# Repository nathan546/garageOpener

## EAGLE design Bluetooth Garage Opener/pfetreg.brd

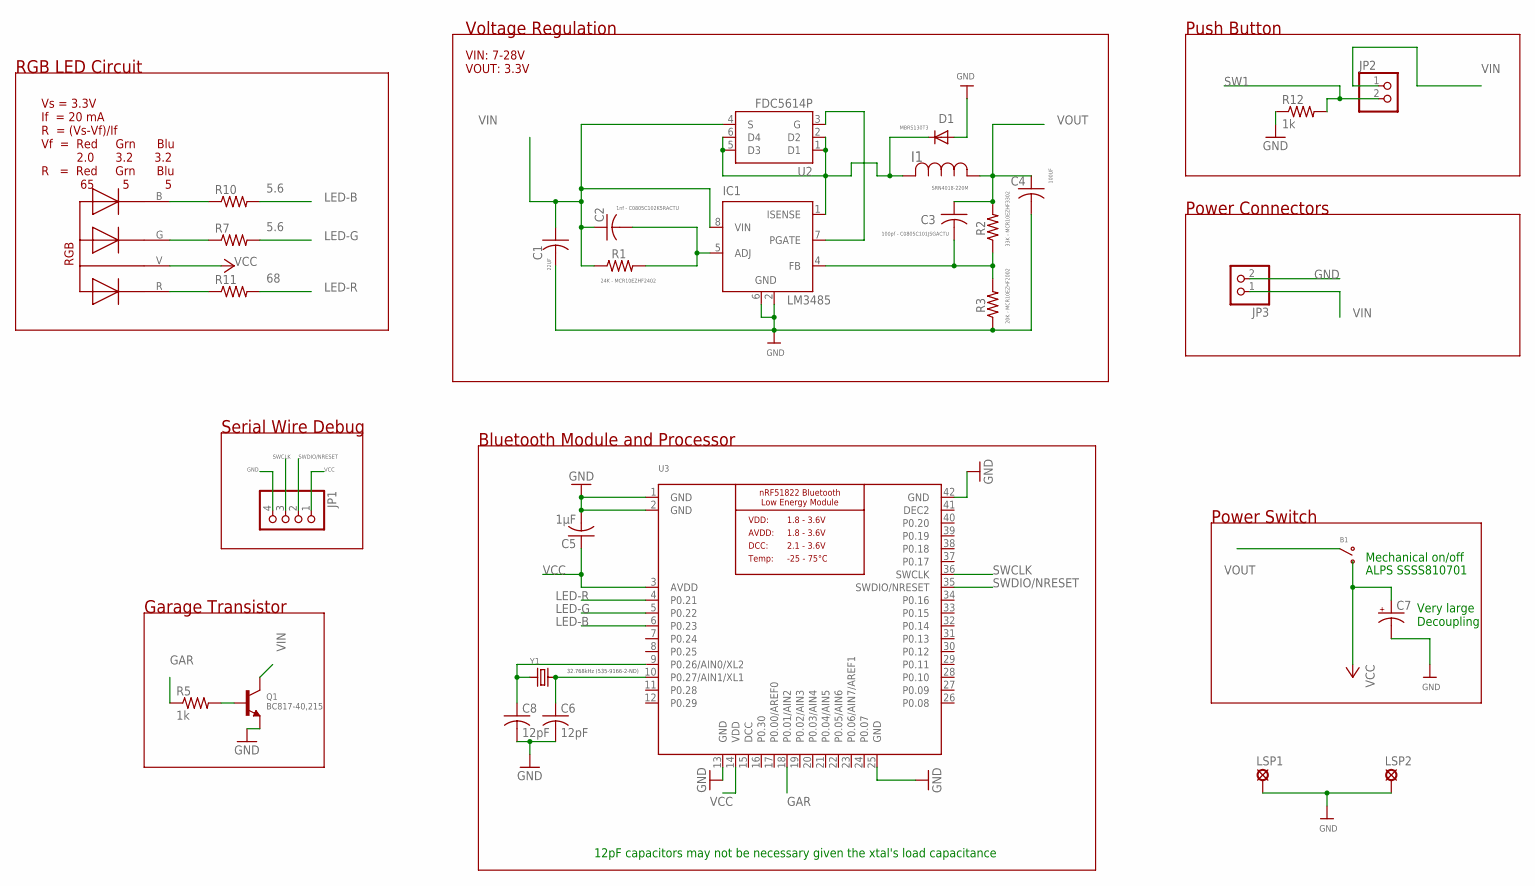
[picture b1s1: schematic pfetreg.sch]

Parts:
B1: SSSS810701
C1: 22UF; CAPCP7343X430N
C2: 1nf - C0805C102K5RACTU; C0805K
C3: 100pf - C0805C101J5GACTU; C0805K
C4: 100UF; CAPCP7343X430N
C5: 1µF; C0805K
C6, C8: 12pF; C0805
C7: CPOL-USE5-10.5; E5-10,5
D1: MBRS130T3; DO214AA
I1: SRN4018-220M
IC1: LM3485; MSOP08
JP1: PINHD-1X4; 1X04
JP2, JP3: PINHD-1X2; 1X02
LSP1, LSP2: LSP11
Q1: BC817-40,215; SOT23-R
R1: 24K - MCR10EZHF2402; R0805W
R2: 33K - MCR10EZHF3302; R0805W
R3: 20K - MCR10EZHF2002; R0805W
R5, R12: 1k; R0805
R7, R10: 5.6; R0805
R11: 68; R0805
RGB: 5MMRGBLED; LED5MMRGB
U2: FDC5614PSOT-23; SOT23-6
U3: NRF51822_MODULE_MDBT40; BLE_MODULE_RAYTAC_MDBT40
Y1: CRYSTAL8X3.8SMT; CRYSTAL_8X3.8

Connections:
DCC: U3.15 (DCC)
DEC2: U3.41 (DEC2)
GAR: R5.1, U3.18 (P0.01/AIN2)
GND: C1.2 (I2), C4.2 (I2), C5.2, C6.2, C7.-, C8.2, D1.A, IC1.2 (GND), IC1.6 (GND), JP1.4, JP3.2, LSP1.MP, LSP2.MP, Q1.2 (E), R3.1, R12.1, U3.1 (GND), U3.2 (GND), U3.13 (GND), U3.25 (GND), U3.42 (GND)
LED-B: R10.2, U3.6 (P0.23)
LED-G: R7.2, U3.5 (P0.22)
LED-R: R11.2, U3.4 (P0.21)
unnamed: D1.C, I1.1 (I1), IC1.1 (ISENSE), U2.1 (D1), U2.2 (D2), U2.5 (D3), U2.6 (D4)
unnamed: C3.2, IC1.4 (FB), R2.1, R3.2
unnamed: IC1.7 (PGATE), U2.3 (G)
unnamed: C2.2, IC1.5 (ADJ), R1.2
unnamed: Q1.1 (B), R5.2
unnamed: R7.1, RGB.G
unnamed: R10.1, RGB.B
unnamed: R11.1, RGB.R
unnamed: C8.1, U3.9 (P0.26/AIN0/XL2), Y1.P$1 (1)
unnamed: C6.1, U3.10 (P0.27/AIN1/XL1), Y1.P$4 (2)
SW1: JP2.2, R12.2
SWCLK: JP1.3, U3.36 (SWCLK)
SWDIO/NRESET: JP1.2, U3.35 (SWDIO/NRESET)
VCC: B1.1 (B), C5.1, C7.+, JP1.1, RGB.V, U3.3 (AVDD), U3.14 (VDD)
VIN: C1.1 (I1), C2.1, IC1.8 (VIN), JP2.1, JP3.1, Q1.3 (C), R1.1, U2.4 (S)
VOUT: B1.2 (COM), C3.1, C4.1 (I1), I1.2 (I2), R2.2

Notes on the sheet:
VIN: 7-28V VOUT: 3.3V
32.768kHz (535-9166-2-ND)
Bluetooth Module and Processor
12pF capacitors may not be necessary given the xtal's load capacitance
Vs = 3.3V If = 20 mA R = (Vs-Vf)/If Vf = Red Grn Blu 2.0 3.2 3.2 R = Red Grn Blu 65 5 5
RGB LED Circuit
Voltage Regulation
Push Button
Power Switch
Mechanical on/off
ALPS SSSS810701
Serial Wire Debug
Garage Transistor
Power Connectors
Very large Decoupling

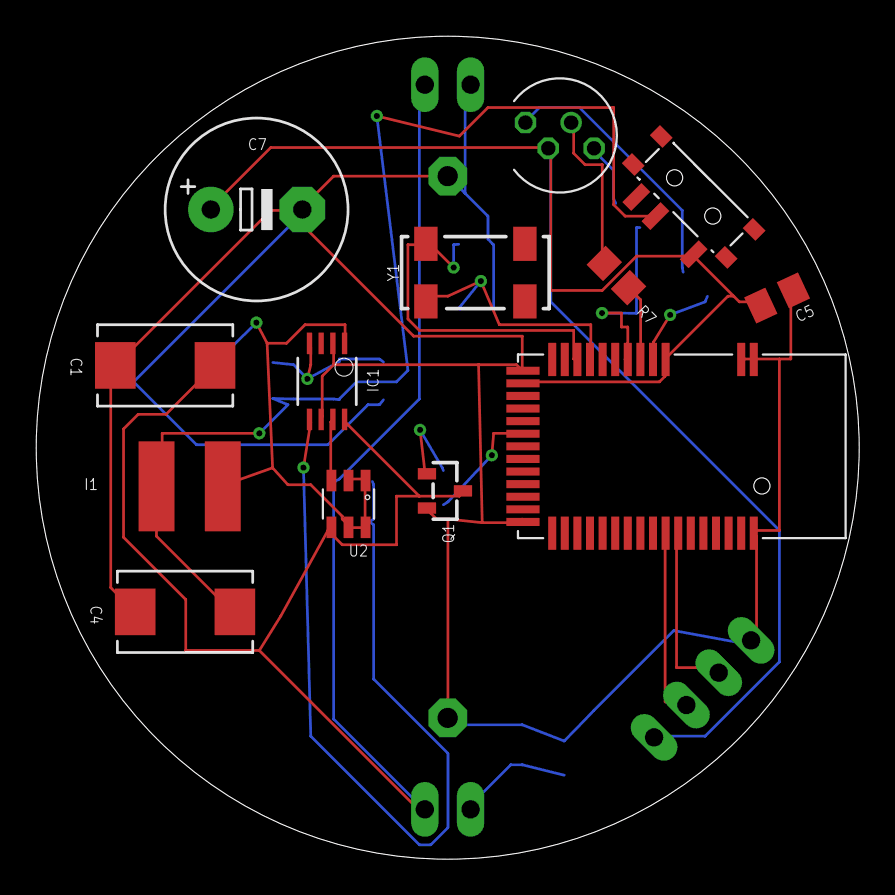
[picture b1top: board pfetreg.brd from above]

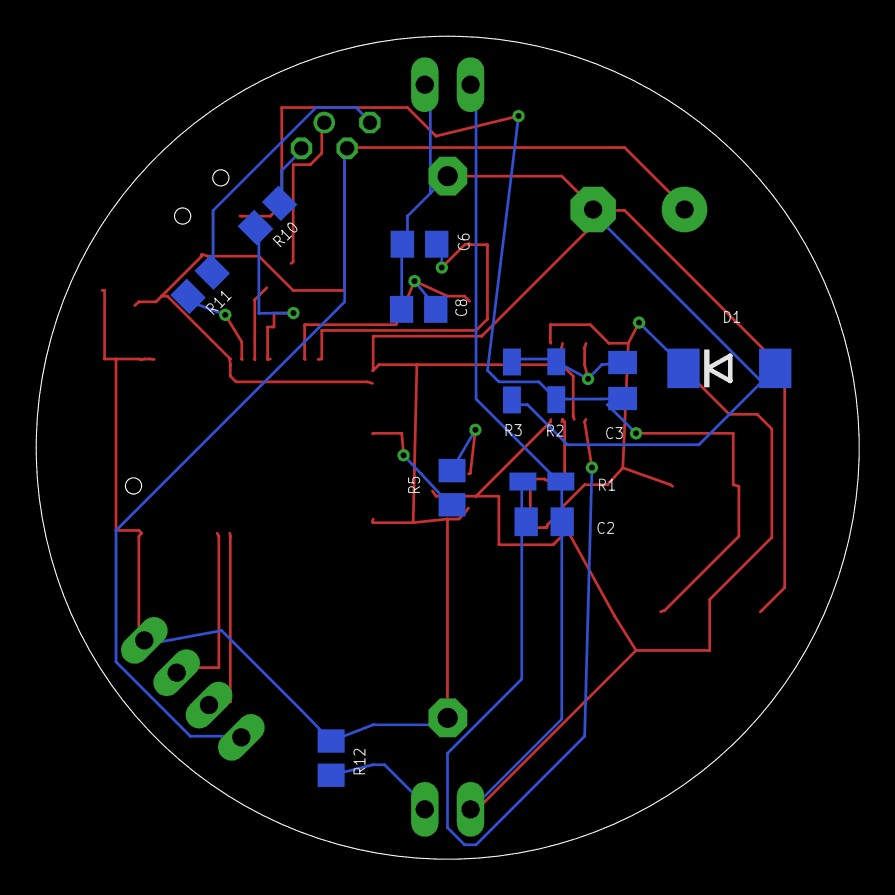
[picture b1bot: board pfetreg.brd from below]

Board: 2 copper layers, 45.7 x 45.7 mm, 30 parts (12 on the bottom side), 21 nets.

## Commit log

2016-12-15 Added source code
